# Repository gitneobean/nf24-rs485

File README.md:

# nf24-rs485
协议转换器

## 项目说明<br>
本项目的主要功能是将有线RS485数据通过RF24发送出去或将RS24接收到的数据转发到RS485上<br>
本项目包括 电路设计图、PCB以及mcu的C代码实现<br>

## 目录说明<br>
kicad：基于kicad设计的电路原理图和PCB（mcu为cx32l003）<br>
iar：基于iar编写的程序源代码<br>
python：基于python编写的转换器配置工具<br>
release：pcb制造文件和编译好的二进制烧录文件<br>

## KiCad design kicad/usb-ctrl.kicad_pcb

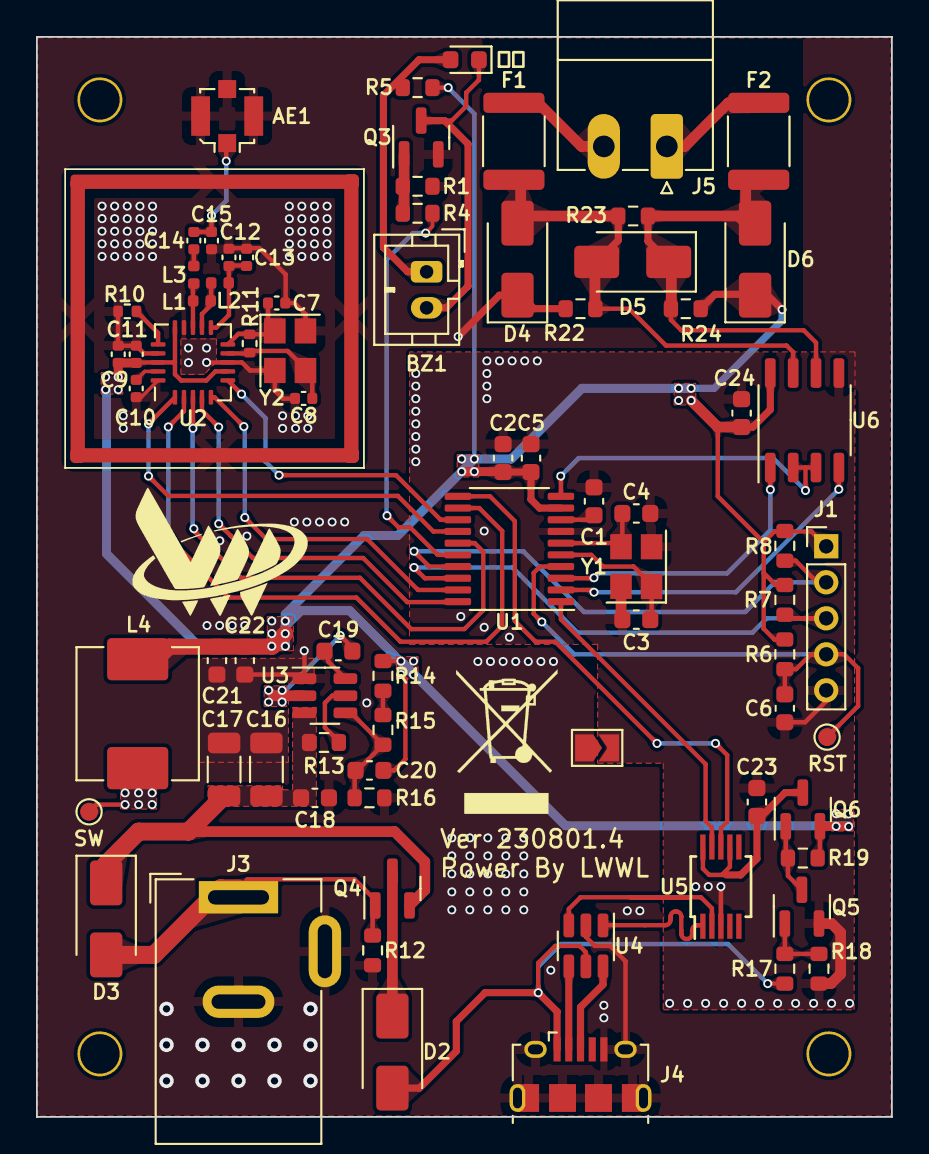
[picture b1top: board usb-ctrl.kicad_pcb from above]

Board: 2 copper layers, 47.5 x 60.0 mm, 81 parts (0 on the bottom side), 53 nets.

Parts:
AE1: Antenna_Shield; U.FL_Molex_MCRF_73412-0110_Vertical
BZ1: Buzzer; JST_PH_B2B-PH-K_1x02_P2.00mm_Vertical
C1: 1uF; C_0603_1608Metric
C2: 4.7uF; C_0603_1608Metric
C3, C4: 22pF; C_0603_1608Metric
C5, C6, C18, C19, C23, C24: 104; C_0603_1608Metric
C7, C8: 22pF; C_0402_1005Metric
C9: 103; C_0402_1005Metric
C10: 333; C_0402_1005Metric
C11: 102; C_0402_1005Metric
C12: 222; C_0402_1005Metric
C13: 4.7pF; C_0402_1005Metric
C14: 1.5pF; C_0402_1005Metric
C15: 1.0pF; C_0402_1005Metric
C16, C17: 106; C_1206_3216Metric
C20: ?; C_0603_1608Metric
C21, C22: 226; C_0603_1608Metric
D1: STAT; LED_0603_1608Metric
D2, D3: SS24; D_SMA
D4, D5, D6: 6V8C; D_SMA
F1, F2: Fuse_Small; Fuse_1812_4532Metric
H2: 左下; R2R2-5_THT
H3: 右上; R2R2-5_THT
H4: 右下; R2R2-5_THT
J1: SWD; PinHeader_1x05_P2.00mm_Vertical
J2: RFShield_OnePiece; shield-24l01
J3: POWER-DRV; BarrelJack_Wuerth_6941xx301002
J4: USB_B_Micro; USB_Micro-B_Amphenol_10118194_Horizontal
J5: RS485-R; PhoenixContact_MC_1,5_2-G-3.5_1x02_P3.50mm_Horizontal
JP1: 接地; SolderJumper-2_P1.3mm_Open_TrianglePad1.0x1.5mm
L1: 8.2nH; L_0402_1005Metric
L2: 2.7nH; L_0402_1005Metric
L3: 3.9nH; L_0402_1005Metric
L4: 2.2uH; L_Abracon_ASPI-0630LR
Q3, Q5: SS8050; SOT-23
Q4, Q6: AO3401A; SOT-23
R1, R12, R18: 100K; R_0603_1608Metric
R4, R22, R24: 4.7K; R_0603_1608Metric
R5, R6, R7, R8, R13, R15, R16, R17: 10K; R_0603_1608Metric
R10: 22K; R_0402_1005Metric
R11: 1M; R_0402_1005Metric
R14: 22K; R_0603_1608Metric
R19: 20K; R_0603_1608Metric
R23: 120; R_0603_1608Metric
TP1: RESET; TestPoint_Pad_D1.0mm
TP2: 示波器探测; TestPoint_Pad_D1.0mm
U1: CX32L003F8P6; TSSOP-20_4.4x6.5mm_P0.65mm
U2: NRF24L01; QFN-20-4x4mm_P0.5mm_EP2.5x2.5mm
U3: TPS563201; SOT-23-6
U4: USBLC6-2SC6; SOT-23-6
U5: CH340X; MSOP-10_3x3mm_P0.5mm
U6: MAX3485; SOP-8_3.9x4.9mm_P1.27mm
Y1: 22.1184MHz; Crystal_SMD_3225-4Pin_3.2x2.5mm
Y2: 16MHz; Crystal_SMD_3225-4Pin_3.2x2.5mm
locked: 左上; R2R2-5_THT

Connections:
/3V3: C2.1, C5.1, C9.1, C11.1, C20.2, C21.2, C22.2, C24.1, D6.1 (A1), J1.1, L4.2, Q6.2 (S), R5.1, R6.1, R7.1, R8.1, R14.2, R19.1, R24.2, U1.9 (VDD), U2.7 (VDD), U2.15 (VDD), U2.18 (VDD), U6.8 (VCC)
/DIR-R: U1.10 (PA3), U6.2 (~RE), U6.3 (DE)
/NRST: C6.2, J1.4, R6.2, TP1.1, U1.4 (NRST)
/OSC_IN: C3.1, U1.5 (OSCIN/PA1), Y1.1
/OSC_OUT: C4.2, U1.6 (OSCOUT/PA2), Y1.3
/RF-CE: U1.14 (PC4/AIN2), U2.1 (CE)
/RF-IRQ: U1.13 (PC3/AIN1), U2.6 (IRQ)
/RF-MISO: U1.19 (PD2/AIN3/VCIN0), U2.5 (MISO)
/RF-MOSI: U1.20 (PD3/AIN4), U2.4 (MOSI)
/RF-NSS: U1.12 (PB4/X32K_OUT), U2.2 (CSN)
/RF-SCK: U1.15 (PC5/VCIN1), U2.3 (SCK)
/RXD-R: U1.3 (AIN6/PD6), U6.1 (RO)
/RXD-U: U1.11 (PB5/X32K_IN), U5.8 (TXD)
/STAT: R4.1, U1.16 (PC6/AIN0)
/SWCLK: J1.3, R7.2, U1.18 (PD1/SWDCLK)
/SWDIO: J1.2, R8.2, U1.17 (PC7/SWDIO)
/TXD-R: U1.2 (AIN5/PD5), U6.4 (DI)
/TXD-U: U1.1 (VCIN2/PD4), U5.9 (RXD)
/nrf24l01/ANT: AE1.1 (A), C14.2, C15.1
/nrf24l01/OSC_IN: C7.1, R11.2, U2.10 (XC1), Y2.1
/nrf24l01/OSC_OUT: C8.2, R11.1, U2.9 (XC2), Y2.3
/power/D+: J4.3 (D+), U4.6 (I/O1)
/power/D-: J4.2 (D-), U4.4 (I/O2)
/power/SW: C19.2, L4.1, TP2.1, U3.2 (SW)
/power/USB_D+: U4.1 (I/O1), U5.1 (UD+)
/power/USB_D-: U4.3 (I/O2), U5.2 (UD-)
/power/USB_VBUS: D2.2 (A), J4.1 (VBUS), R17.1, U4.5 (VBUS)
/power/V-EXT: D3.2 (A), J3.1, Q4.1 (G), R12.1
/power/VIN: C16.1, C17.1, C18.1, D3.1 (K), Q4.2 (S), R13.1, U3.3 (VIN)
GNDD: C1.2, C2.2, C3.2, C4.1, C5.2, C6.1, C23.2, C24.2, J1.5, JP1.2 (B), Q5.2 (E), R18.2, U1.7 (VSS), U5.3 (GND), U6.5 (GND), Y1.2, Y1.4
GNDPWR: AE1.2 (Shield), C7.2, C8.1, C9.2, C10.2, C11.2, C12.1, C13.1, C15.2, C16.2, C17.2, C18.2, C21.1, C22.1, D4.1 (A1), J2.1 (Shield), J3.2, J3.3, J4.5 (GND), J4.6 (Shield), JP1.1 (A), Q3.2 (E), R1.1, R10.1, R12.2, R16.1, R22.1, U2.8 (VSS), U2.14 (VSS), U2.17 (VSS), U2.20 (VSS), U3.1 (GND), U4.2 (GND), Y2.2, Y2.4
unnamed: BZ1.2 (+), D1.1 (K), Q3.3 (C)
unnamed: BZ1.1 (-), D1.2 (A), R5.2
unnamed: C14.1, L3.2
unnamed: D2.1 (K), Q4.3 (D)
unnamed: D4.2 (A2), D5.2 (A2), F1.2, R22.2, R23.1, U6.7 (B)
unnamed: D5.1 (A1), D6.2 (A2), F2.2, R23.2, R24.1, U6.6 (A)
unnamed: F2.1, J5.1
unnamed: F1.1, J5.2
unnamed: Q3.1 (B), R1.2, R4.2
unnamed: Q5.1 (B), R17.2, R18.1
unnamed: Q5.3 (C), Q6.1 (G), R19.2
unnamed: C23.1, Q6.3 (D), U5.7 (VCC), U5.10 (V3)
unnamed: R14.1, R15.2
unnamed: C1.1, U1.8 (VCAP)
unnamed: L1.1, L2.1, U2.12 (ANT1)
unnamed: L1.2, L3.1, U2.13 (ANT2)
unnamed: C10.1, U2.19 (DVDD)
unnamed: R10.2, U2.16 (IREF)
unnamed: C12.2, C13.2, L2.2, U2.11 (VDD_PA)
unnamed: R13.2, U3.5 (EN)
unnamed: C19.1, U3.6 (VBST)
unnamed: C20.1, R15.1, R16.2, U3.4 (VFB)
